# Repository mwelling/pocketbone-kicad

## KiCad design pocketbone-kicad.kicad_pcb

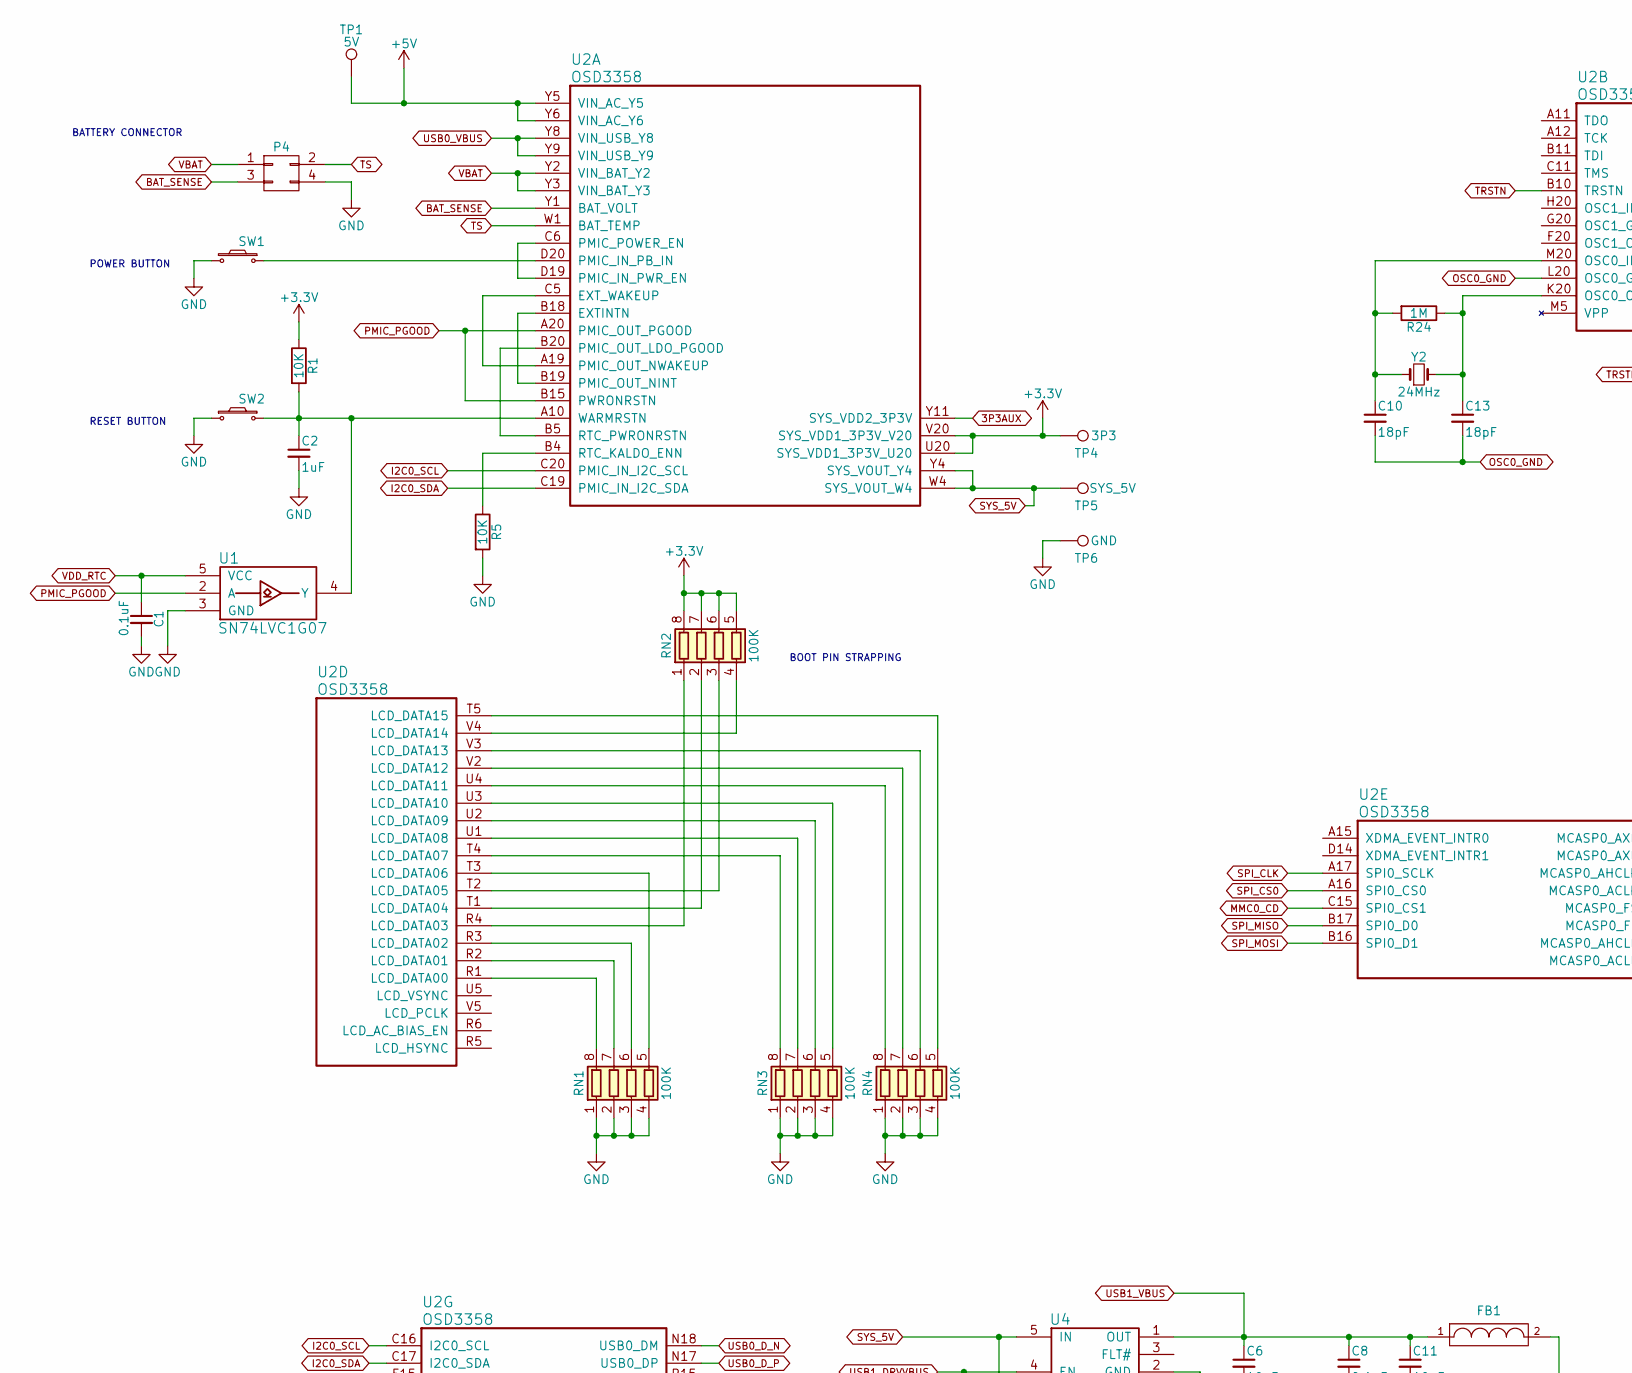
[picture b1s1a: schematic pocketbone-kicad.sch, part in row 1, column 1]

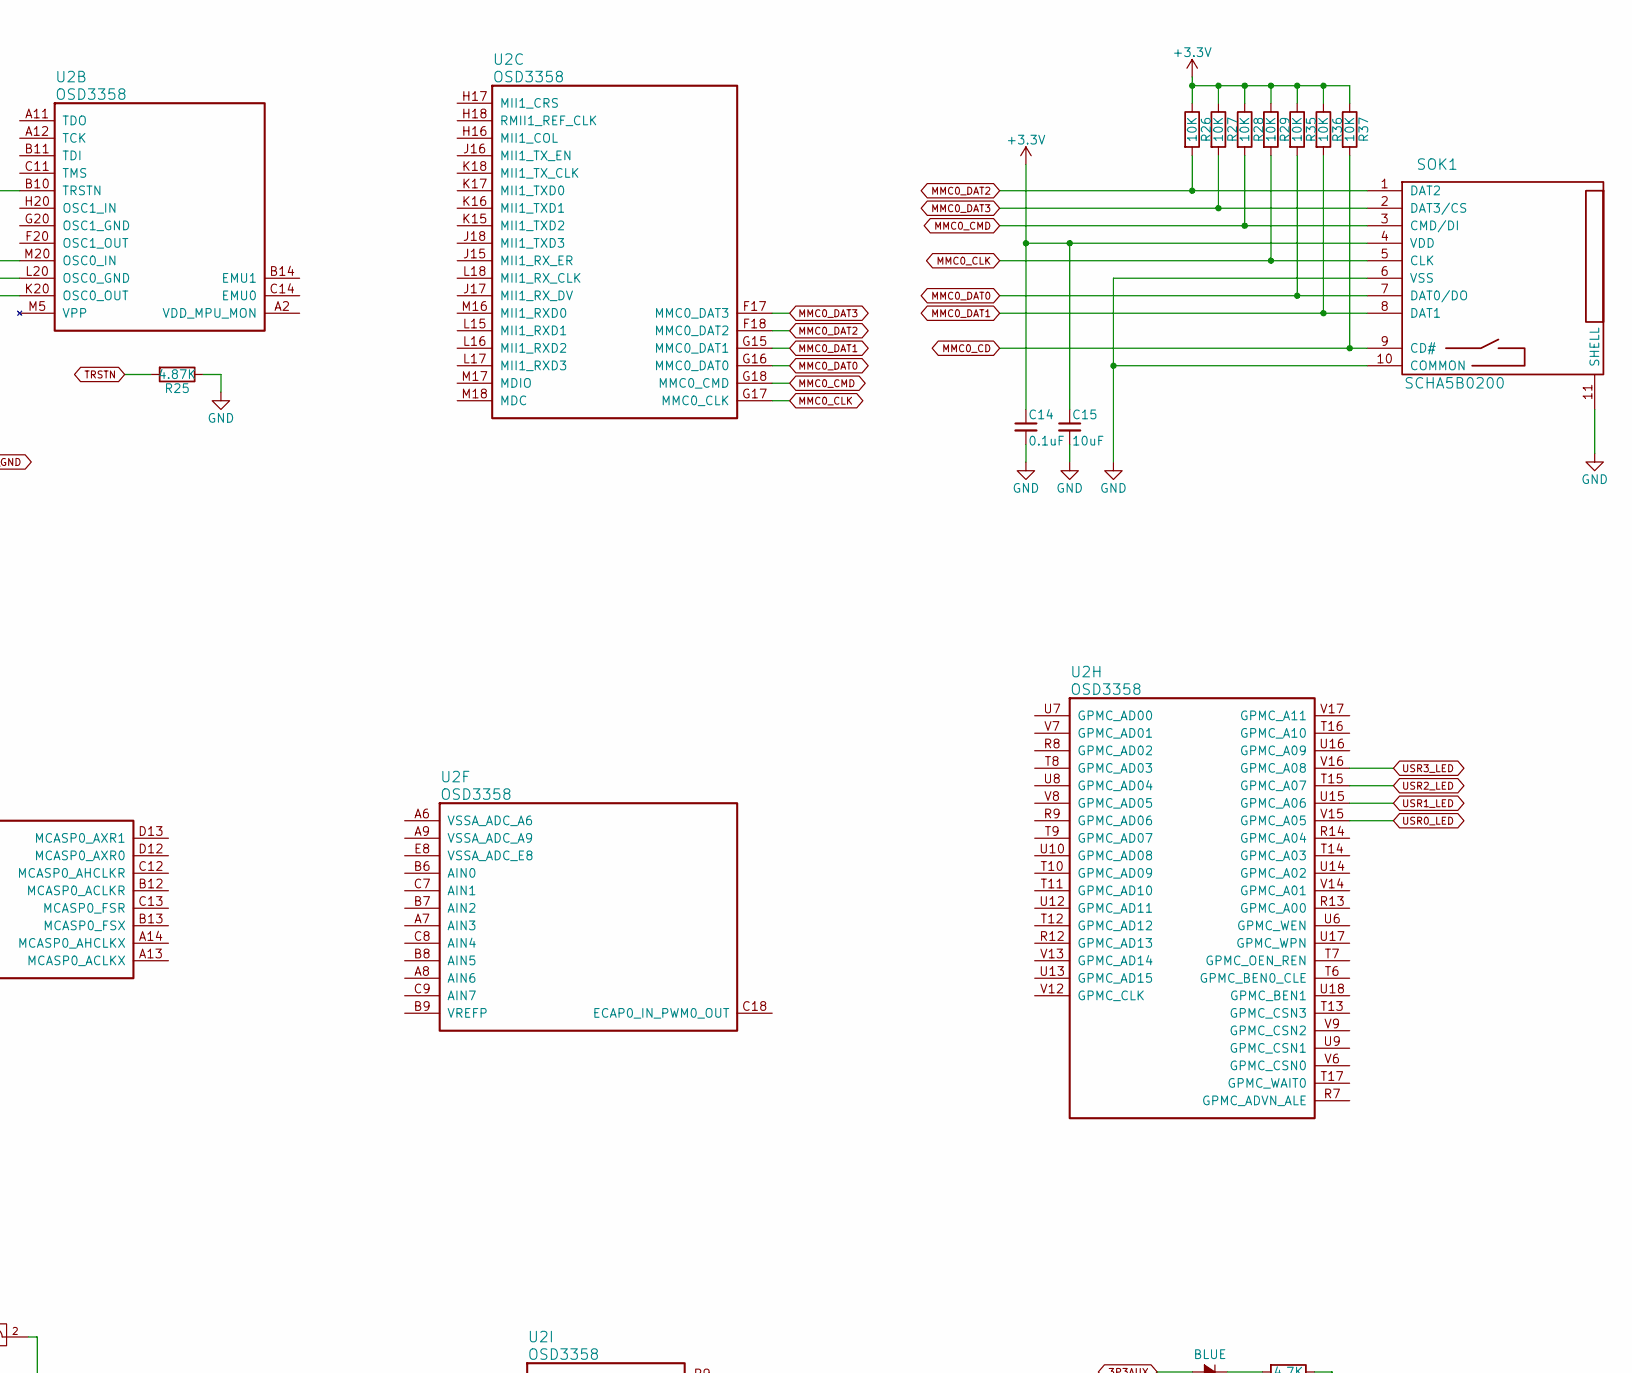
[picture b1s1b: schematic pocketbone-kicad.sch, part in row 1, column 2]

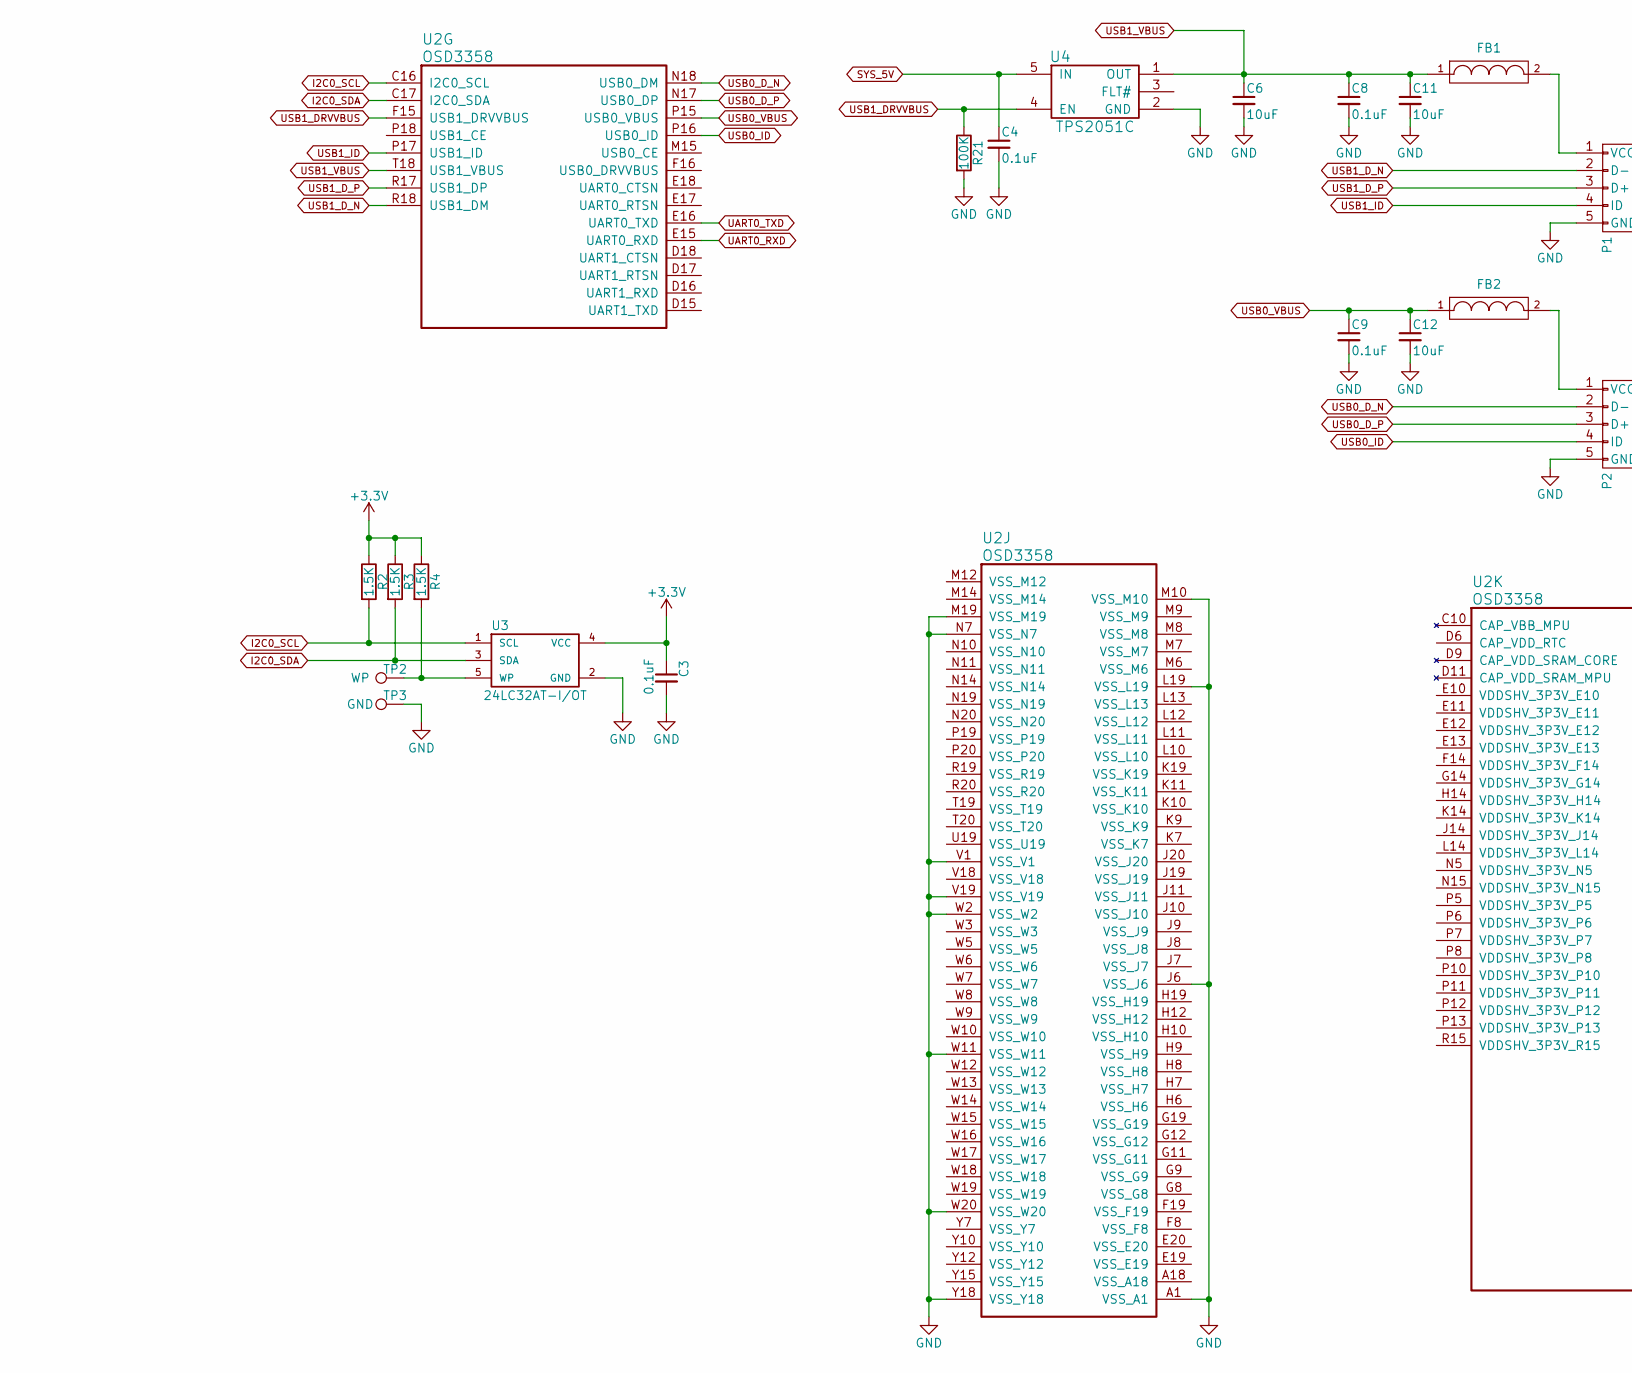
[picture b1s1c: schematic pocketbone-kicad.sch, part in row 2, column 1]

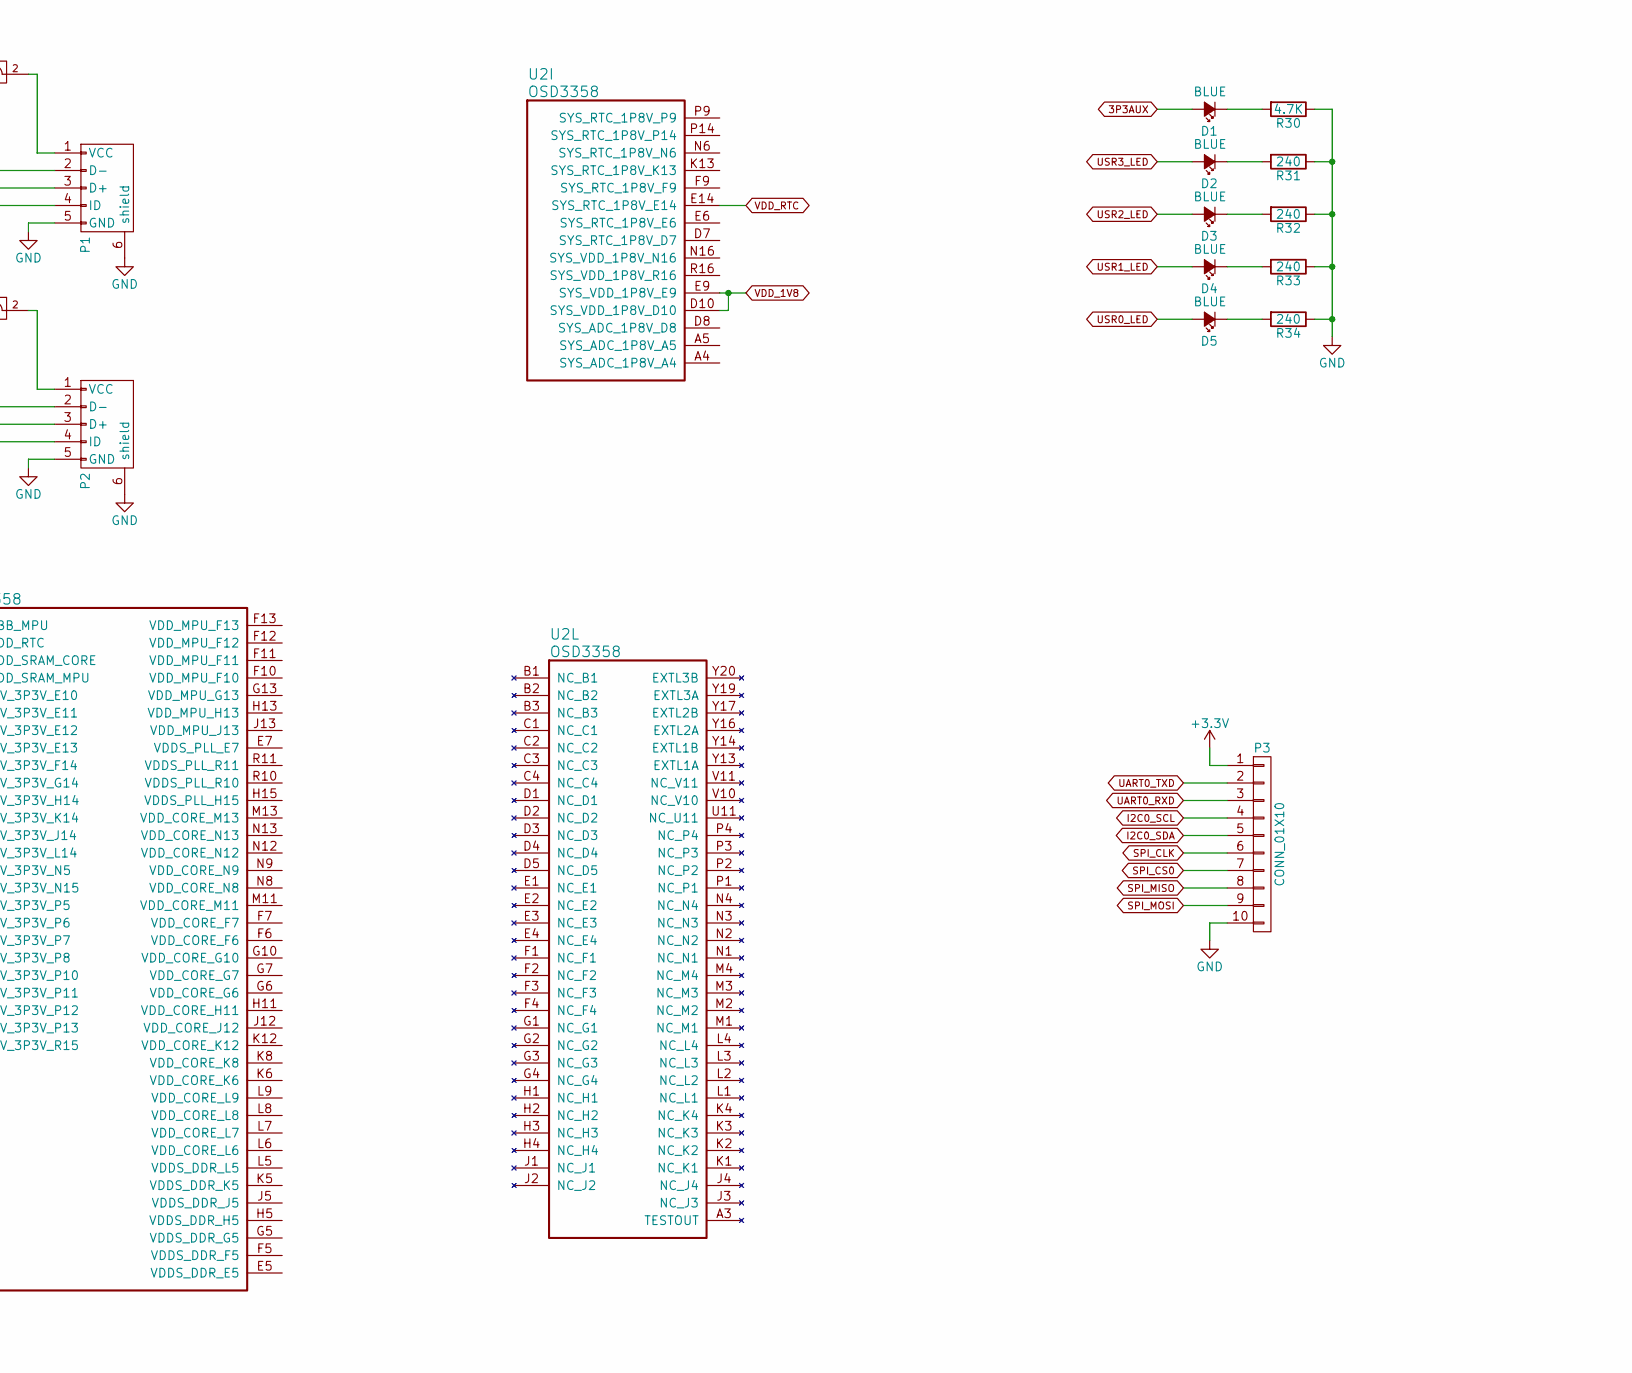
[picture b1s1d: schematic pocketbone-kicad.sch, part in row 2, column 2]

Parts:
C1, C3, C4, C8, C9, C14: 0.1uF; C_0402
C2: 1uF; C_0402
C6, C11, C12, C15: 10uF; C_0603
C10, C13: 18pF; C_0402
D1, D2, D3, D4, D5: BLUE; LED-0603
FB1, FB2: FILTER; C_0603
P1, P2: USB_OTG; USB_MICRO_B_ST-USB-001E
P3: CONN_01X10; Socket_Strip_Straight_1x10
P4: CONN_02X02; Socket_Strip_Straight_2x02
R1, R5, R26, R27, R28, R29, R35, R36, R37: 10K; R_0402
R2, R3, R4: 1.5K; R_0402
R21: 100K; R_0402
R24: 1M; R_0402
R25: 4.87K; R_0402
R30: 4.7K; R_0402
R31, R32, R33, R34: 240; R_0402
RN1, RN2, RN3, RN4: 100K; R_Array_Concave_4x0603
SOK1: SCHA5B0200
SW1, SW2: SW_PUSH_SMALL_H; SW_SPST_EVQPE1
TP1: 5V; Measurement_Point_Round-SMD-Pad_Small
TP2: WP; Measurement_Point_Round-SMD-Pad_Small
TP3, TP6: GND; Measurement_Point_Round-SMD-Pad_Small
TP4: 3P3; Measurement_Point_Round-SMD-Pad_Small
TP5: SYS_5V; Measurement_Point_Round-SMD-Pad_Small
U1: SN74LVC1G07; SOT-23-5
U2: OSD3358; BGA-400-1-27mm
U3: 24LC32AT-I/OT; SOT-23-5
U4: TPS2051C; SOT-23-5
Y2: 24MHz; 445C33D24M00000

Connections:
3P3AUX: D1.2 (A), U2.Y11 (SYS_VDD2_3P3V)
+3V3: C3.1, C14.1, C15.1, P3.1, R1.1, R2.1, R3.1, R4.1, R26.1, R27.1, R28.1, R29.1, R35.1, R36.1, R37.1, RN2.5 (R4.2), RN2.6 (R3.2), RN2.7 (R2.2), RN2.8 (R1.2), SOK1.4 (VDD), TP4.1, U2.U20 (SYS_VDD1_3P3V_U20), U2.V20 (SYS_VDD1_3P3V_V20), U3.4 (VCC)
+5V: TP1.1, U2.Y5 (VIN_AC_Y5), U2.Y6 (VIN_AC_Y6)
BAT_SENSE: P4.3, U2.Y1 (BAT_VOLT)
GND: C1.2, C2.2, C3.2, C4.2, C6.2, C8.2, C9.2, C11.2, C12.2, C14.2, C15.2, P1.5 (GND), P1.6 (shield), P1.7, P1.8, P1.9, P2.5 (GND), P2.6 (shield), P2.7, P2.8, P2.9, P3.10, P4.4, R5.2, R21.2, R25.1, R30.1, R31.1, R32.1, R33.1, R34.1, RN1.1 (R1.1), RN1.2 (R2.1), RN1.3 (R3.1), RN1.4 (R4.1), RN3.1 (R1.1), RN3.2 (R2.1), RN3.3 (R3.1), RN3.4 (R4.1), RN4.1 (R1.1), RN4.2 (R2.1), RN4.3 (R3.1), RN4.4 (R4.1), SOK1.6 (VSS), SOK1.10 (COMMON), SOK1.11 (SHELL), SW1.1, SW2.1, TP3.1, TP6.1, U1.3 (GND), U2.A1 (VSS_A1), U2.J6 (VSS_J6), U2.L19 (VSS_L19), U2.M10 (VSS_M10), U2.M19 (VSS_M19), U2.N7 (VSS_N7), U2.V1 (VSS_V1), U2.V19 (VSS_V19), U2.W2 (VSS_W2), U2.W11 (VSS_W11), U2.W20 (VSS_W20), U2.Y18 (VSS_Y18), U3.2 (GND), U4.2 (GND)
I2C0_SCL: P3.4, R2.2, U2.C16 (I2C0_SCL), U2.C20 (PMIC_IN_I2C_SCL), U3.1 (SCL)
I2C0_SDA: P3.5, R3.2, U2.C17 (I2C0_SDA), U2.C19 (PMIC_IN_I2C_SDA), U3.3 (SDA)
MMC0_CD: R37.2, SOK1.9 (CD#), U2.C15 (SPI0_CS1)
MMC0_CLK: R29.2, SOK1.5 (CLK), U2.G17 (MMC0_CLK)
MMC0_CMD: R28.2, SOK1.3 (CMD/DI), U2.G18 (MMC0_CMD)
MMC0_DAT0: R35.2, SOK1.7 (DAT0/DO), U2.G16 (MMC0_DAT0)
MMC0_DAT1: R36.2, SOK1.8 (DAT1), U2.G15 (MMC0_DAT1)
MMC0_DAT2: R26.2, SOK1.1 (DAT2), U2.F18 (MMC0_DAT2)
MMC0_DAT3: R27.2, SOK1.2 (DAT3/CS), U2.F17 (MMC0_DAT3)
unnamed: C2.1, R1.2, SW2.2, U1.4 (Y), U2.A10 (WARMRSTN)
unnamed: C10.1, R24.2, U2.M20 (OSC0_IN), Y2.1
unnamed: C13.1, R24.1, U2.K20 (OSC0_OUT), Y2.2
unnamed: D1.1 (K), R30.2
unnamed: D2.1 (K), R31.2
unnamed: D3.1 (K), R32.2
unnamed: D4.1 (K), R33.2
unnamed: D5.1 (K), R34.2
unnamed: FB1.2, P1.1 (VCC)
unnamed: FB2.2, P2.1 (VCC)
unnamed: R4.2, TP2.1, U3.5 (WP)
unnamed: R5.1, U2.B4 (RTC_KALDO_ENN)
unnamed: RN1.5 (R4.2), U2.T3 (LCD_DATA06)
unnamed: RN1.6 (R3.2), U2.R3 (LCD_DATA02)
unnamed: RN1.7 (R2.2), U2.R2 (LCD_DATA01)
unnamed: RN1.8 (R1.2), U2.R1 (LCD_DATA00)
unnamed: RN2.1 (R1.1), U2.R4 (LCD_DATA03)
unnamed: RN2.2 (R2.1), U2.T1 (LCD_DATA04)
unnamed: RN2.3 (R3.1), U2.T2 (LCD_DATA05)
unnamed: RN2.4 (R4.1), U2.V4 (LCD_DATA14)
unnamed: RN3.5 (R4.2), U2.U3 (LCD_DATA10)
unnamed: RN3.6 (R3.2), U2.U2 (LCD_DATA09)
unnamed: RN3.7 (R2.2), U2.U1 (LCD_DATA08)
unnamed: RN3.8 (R1.2), U2.T4 (LCD_DATA07)
unnamed: RN4.5 (R4.2), U2.T5 (LCD_DATA15)
unnamed: RN4.6 (R3.2), U2.V3 (LCD_DATA13)
unnamed: RN4.7 (R2.2), U2.V2 (LCD_DATA12)
unnamed: RN4.8 (R1.2), U2.U4 (LCD_DATA11)
unnamed: SW1.2, U2.D20 (PMIC_IN_PB_IN)
unnamed: U2.A19 (PMIC_OUT_NWAKEUP), U2.C5 (EXT_WAKEUP)
unnamed: U2.B18 (EXTINTN), U2.B19 (PMIC_OUT_NINT)
unnamed: U2.B5 (RTC_PWRONRSTN), U2.B20 (PMIC_OUT_LDO_PGOOD)
unnamed: U2.C6 (PMIC_POWER_EN), U2.D19 (PMIC_IN_PWR_EN)
OSC0_GND: C10.2, C13.2, U2.L20 (OSC0_GND)
PMIC_PGOOD: U1.2 (A), U2.A20 (PMIC_OUT_PGOOD), U2.B15 (PWRONRSTN)
SPI_CLK: P3.6, U2.A17 (SPI0_SCLK)
SPI_CS0: P3.7, U2.A16 (SPI0_CS0)
SPI_MISO: P3.8, U2.B17 (SPI0_D0)
SPI_MOSI: P3.9, U2.B16 (SPI0_D1)
SYS_5V: C4.1, TP5.1, U2.W4 (SYS_VOUT_W4), U2.Y4 (SYS_VOUT_Y4), U4.5 (IN)
TRSTN: R25.2, U2.B10 (TRSTN)
TS: P4.2, U2.W1 (BAT_TEMP)
UART0_RXD: P3.3, U2.E15 (UART0_RXD)
UART0_TXD: P3.2, U2.E16 (UART0_TXD)
USB0_D_N: P2.2 (D-), U2.N18 (USB0_DM)
USB0_D_P: P2.3 (D+), U2.N17 (USB0_DP)
USB0_ID: P2.4 (ID), U2.P16 (USB0_ID)
USB0_VBUS: C9.1, C12.1, FB2.1, U2.P15 (USB0_VBUS), U2.Y8 (VIN_USB_Y8), U2.Y9 (VIN_USB_Y9)
USB1_DRVVBUS: R21.1, U2.F15 (USB1_DRVVBUS), U4.4 (EN)
USB1_D_N: P1.2 (D-), U2.R18 (USB1_DM)
USB1_D_P: P1.3 (D+), U2.R17 (USB1_DP)
USB1_ID: P1.4 (ID), U2.P17 (USB1_ID)
USB1_VBUS: C6.1, C8.1, C11.1, FB1.1, U2.T18 (USB1_VBUS), U4.1 (OUT)
USR0_LED: D5.2 (A), U2.V15 (GPMC_A05)
USR1_LED: D4.2 (A), U2.U15 (GPMC_A06)
USR2_LED: D3.2 (A), U2.T15 (GPMC_A07)
USR3_LED: D2.2 (A), U2.V16 (GPMC_A08)
VBAT: P4.1, U2.Y2 (VIN_BAT_Y2), U2.Y3 (VIN_BAT_Y3)
VDD_1V8: U2.D10 (SYS_VDD_1P8V_D10), U2.E9 (SYS_VDD_1P8V_E9)
VDD_RTC: C1.1, U1.5 (VCC), U2.E14 (SYS_RTC_1P8V_E14)

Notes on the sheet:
POWER BUTTON
RESET BUTTON
BOOT PIN STRAPPING
BATTERY CONNECTOR

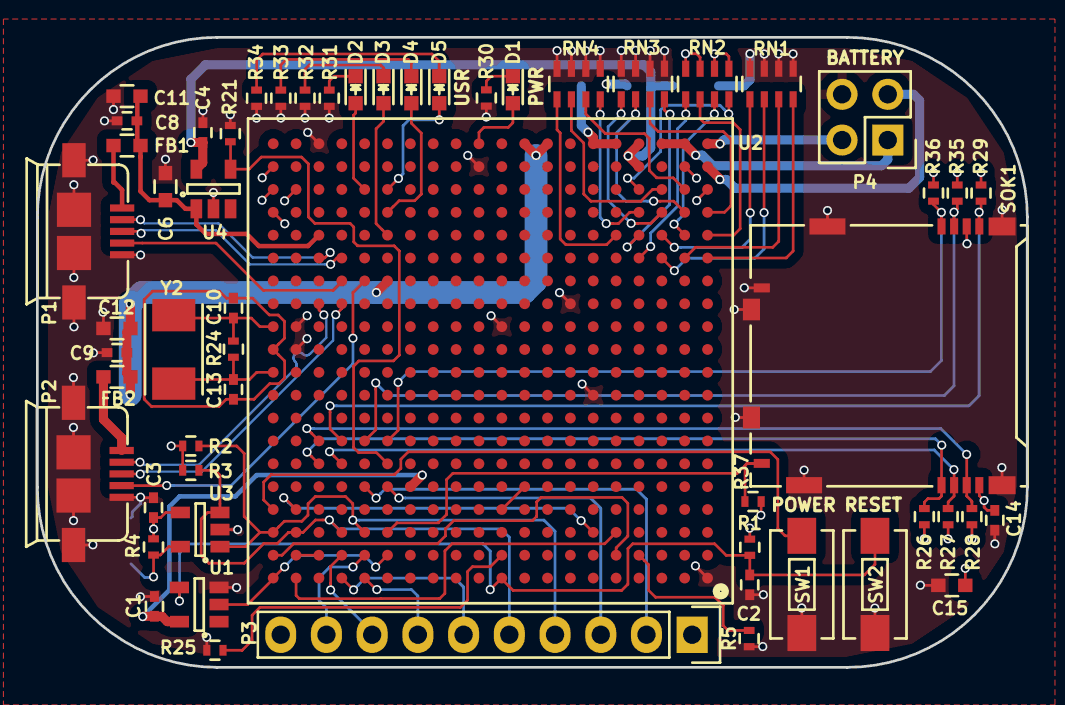
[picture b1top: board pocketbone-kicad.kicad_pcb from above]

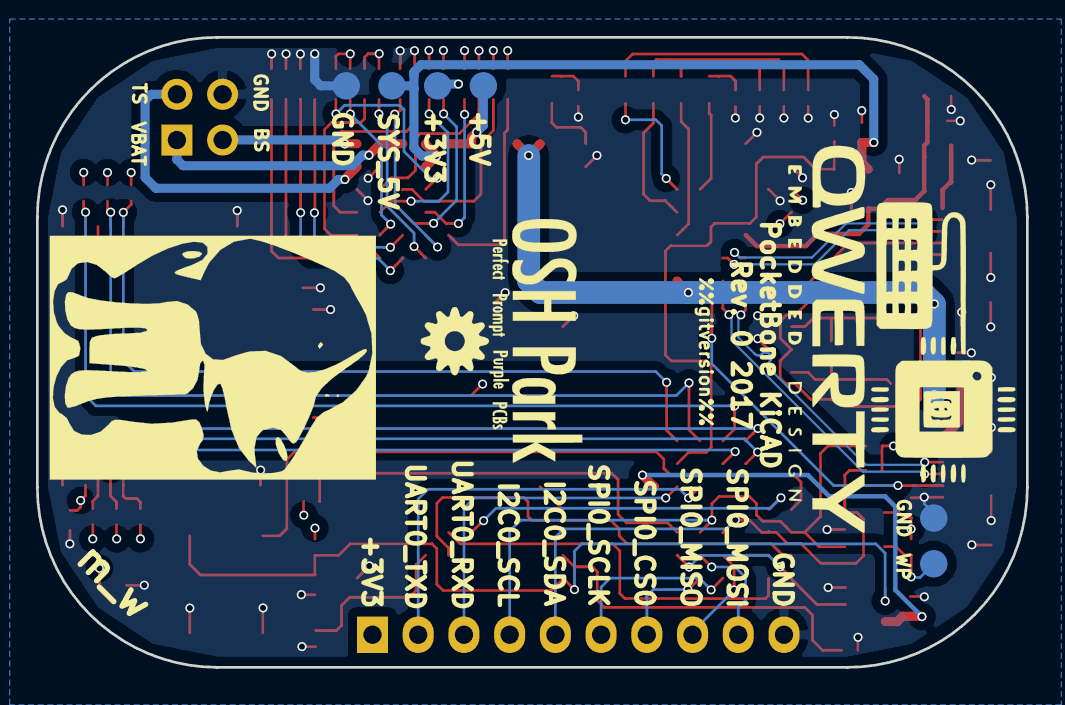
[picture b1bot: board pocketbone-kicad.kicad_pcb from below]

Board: 4 copper layers, 55.0 x 35.0 mm, 62 parts (6 on the bottom side), 74 nets.

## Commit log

2016-04-18 Add ground plane
2016-04-18 Consolidate library
    * Renumber parts
2016-04-18 Update some ref designators
2016-04-18 Rename USB connectors
2016-04-18 Resize some silkscreen
2016-04-18 Reposition components
2016-04-18 Routed USB1 DP/DN
2016-04-18 Routed USB0 DP/DN
2016-04-18 New rough placement
2016-04-18 Hack layout
2016-04-18 Adjusted resistors for 100% layout
2016-05-17 Connect microSD to 3.3V
2016-06-01 Tent vias
2016-11-22 Add README
2016-11-22 Add initial schematic conversion
    TODO:
    - Add buffer to drive reset with POR
    - Add header for expansion
    - Consider adding alternate power input
2016-11-22 Add schematic print for early review
2016-11-26 Schematic updates
    Adds microsd card
    Adds POR buffer
    Adds VBUS switch for Host mode on USB1
2016-11-26 Add updated schematic print for review
2016-11-27 Start placement of PCB
    TODO:
    Create footprint for microSD card.
    Choose appropriate ferrite bead footprint.
    Create footprint for crystals.
    Check patterns for all components.
2016-11-28 Few PCB updates
    Adds pattern for SD card and 24Mhz SMD crystal.
    Removes 32.768KHz crystal from design.
    Preliminary placement done.
    Need to add test points.
    All patterns need to be verified with specific components.
2016-11-28 Add 3D image to README for bling
2016-12-04 Add 10 pin IO header
2016-12-04 2 layer routing attempt
    TODO: Figure out proper USB routing with 2 layers.
2016-12-04 Update plots and README
2016-12-04 Update front of board 3d image
2017-01-18 Pull back routing and update placement
    The placement and footprint updated for USB.
    TODO: Attempt single sided population.
2017-02-02 Many PCB updates
    Updated the placement for single sided population.
    Switched boot mode selection resistors to arrays to save space.
    Switched expansion header to .1 inch (lichen pub compatible).
    Added battery connect similar to BBB.
2017-02-02 Update PDF with schematic changes
2017-02-09 Routing complete
    Battery header updated in schmatic.
    Plots and pictures updated.
    Ready for design review.
2017-02-09 Last minute tweaks
    This version is posted to OSHpark site for anyone to order.
    Order at your own risk.
2017-02-09 Update plots to the latest version
2017-02-10 Add OSHPark logo to the PCB and tweak the silk
    OSHPark sponsoring the first proto run. \o/
    https://oshpark.com/shared_projects/b7F6qftP
2017-02-10 Add an open hardware compatible license
    CERN OHL V1.2
2017-02-13 Updated Footprint and Schematic Librarys
    The Paths of the USB and SOT Footprints pointed to local Directorys on
    your HDD instead of the Project Folder
2017-03-01 Move EAGLE files to a subdirectory
2017-03-01 Remove EAGLE files
2017-03-01 Remove old .gitignore
2017-03-19 o Add Python script that can generate fabbing files from the command line. o Add Makefile that makes use of it: just calling 'make' will create a zip file with the necessary layers. o Send kicad_pcb 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
2017-03-23 o Limit changes in PCB file to only include the %%gitversion%% change.
2017-03-23 o OshPark only successfully recongizes the file names if EdgeCuts is named Edge_Cuts, so renmae that file.
2018-10-02 Testing KiCAD 5 port
